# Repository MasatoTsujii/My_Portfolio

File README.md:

# My Portfolio

## はじめに
本リポジトリは、「アイデア対決・全国高等専門学校ロボットコンテスト（高専ロボコン）」における個人の活動や技術をまとめたポートフォリオ。

主に**回路設計** と **組込みソフトウェア** を担当した。

## 技術要素

| Category | Technology / Tools |
| :--- | :--- |
| **Languages** | C++, C |
| **Firmware** | mbed, PlatformIO, Arduino |
| **Hardware CAD** | KiCad, EAGLE |
| **MCU / Modules** | STM32 (Nucleo), PIC, IM920sL (920MHz), Bluetooth |
| **Others** | Git, VSCode, CAN通信 |

## プロジェクト一覧 (Projects)

各プロジェクトの詳細（ソースコード、回路図、開発背景）は、リンク先のディレクトリに格納。

| Year | Project / Role | Key Technologies |
| :--- | :--- | :--- |
| **2022** | **[Season2022: 自作コントローラー](./Season2022)**<br>操作性向上のための専用ハードウェア開発 | 無線通信, **自作コントローラー**, KiCad |
| **2020** | **[Season2020: ちゃぶ台返しロボット](./Season2020)**<br>ダイレクトティーチングの実装とアーム制御 | **ダイレクトティーチング**, **アーム制御**, mbed, PlatformIO, Eagle |
| **2019** | **[OffSeason2019: オフシーズンプロジェクト](./OffSeason2019)**<br>次期シーズンに向けた要素技術の開発と検証 | モータドライバ設計, 回路設計, EAGLE |
| **2019** | **[Season2019: 洗濯物干しロボット](./Season2019)**<br>初の手動ロボット製作 | 機構理解, チーム開発 |
| **2019-2022** | **[MotorDriver_Projects: モータドライバ開発の軌跡](./MotorDriver_Projects)**<br>自作モータドライバの設計と改良 | **CAN通信**, モータドライバ設計, KiCad, EAGLE, STM32 |

## ハイライト

### 1. 通信環境と操作性の課題解決 (Season2022)
**課題:** 10基の砲塔を個別制御するためのボタン不足と、現地会場での電波干渉（2.4GHz帯）のリスク。

**解決策:**
* **専用コントローラーの自作:** 市販品では不可能なボタン配置と機能を実装。
* **920MHz帯の採用:** 混信に強いIM920sLモジュールを採用し、通信プロトコルを独自に実装・改良。大会での通信エラーはなかった。
* [詳細はこちら](./Season2022)

### 2. ダイレクトティーチングの実装 (Season2020)
**課題:** コロナ禍による活動制限で、複雑なモーションプログラムを組む時間が不足。

**解決策:**
* **直感的な教示システム:** ロボットのアームを手で動かして軌道を記録・再生する機能を実装。
* **成果:** プログラムが書けないメンバーでも演出作成が可能になり、開発効率を向上。「本田技研工業特別賞」を受賞した。
* [詳細はこちら](./Season2020)

### 3. モータドライバの設計と最適化 (MotorDriver_Projects)
**課題:** チーム内での回路のメンテナンス性向上と、通信ノイズによる誤動作の防止。

**解決策:**
* **制御方式:** マイコン1基につき1つのドライバを制御する方式でドライバ内のスイッチを使用し、動作確認を行えるように改良。
* **通信方式とツールの移行:** 通信方式をSPIからノイズに強いCAN通信へ変更し、設計ツールもEAGLEからKiCadへと移行して最適化を図った。
* [詳細はこちら](./MotorDriver_Projects)

---
*Author: [Your Name]*

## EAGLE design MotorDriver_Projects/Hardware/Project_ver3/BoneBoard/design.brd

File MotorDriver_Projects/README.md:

# MotorDriver_Projects

## 概要
これまで作成した表面実装基板の設計データ、およびテスト用ファームウェアをまとめたディレクトリである。
モータドライバの開発コードネームが「Mars（火星）」であったことを発端に、以降製作された電磁弁駆動基板など周辺回路にも惑星の名前が付けられている。
各基板プロジェクトには、CADの元データのほか、閲覧用の回路図（PDF等）および基板レイアウト図が同梱されている。

## ディレクトリ構成とプロジェクトの変遷

### 1. Project_ver1
* **開発ツール:** EAGLE
* **`MD_Mars_ver1`**
    先輩が設計した初期型モータドライバ。メインマイコンに表面実装タイプのPICを採用しており、通信方式はSPIである。

### 2. Project_ver2
* **開発ツール:** EAGLE
* **`MD_Mars_ver2`**
    先輩の`ver1`をベースに、自身で再設計を行ったモデル。製作のしやすさや大会現場でのメンテナンス性を考慮し、マイコンを表面実装からDIP（ピン）タイプのPICへと変更した。通信方式はSPIを継承している。
* **`MD_Mars_study`**
    モータドライバの回路構成や仕組みを深く理解するために自作した学習用基板。部内のCNCルーターで切削加工して製作したが、設計したランド（銅箔部）が細すぎたため、大電流を流した際に焼損した。失敗からプリント基板におけるパターン幅の重要性を学んだ基板である。

### 3. Project_ver3
* **開発ツール:** EAGLE
* **アーキテクチャの刷新**
    「各モータドライバに1つずつマイコンを載せる」方式を廃止し、「1つのメインマイコンで複数のモータドライバを集中制御する」方式へと仕様を大きく変更した。PCのメモリのように、拡張基板に対してドライバを垂直に突き刺して使用する設計を採用している。以下の3つの基板から構成される。
    * **`MD_Mars_ver3`:** モータ駆動回路のみを切り出し、小型化を図ったドライバモジュール。
    * **`MarsBrain`:** メインマイコンからの制御信号を各モータドライバへ分配するための拡張基板。
    * **`BoneBoard`:** メインマイコンとモータドライバ群を相互に接続するためのバックプレーン（骨格）基板。

### 4. Project_ver4
* **開発ツール:** KiCad
* **アーキテクチャの再構築と最適化**
    設計ツールをKiCadへ移行。通信方式をノイズに強いCAN通信へと変更し、新たにゲートドライバICを採用したアップデート版である。
    * **`MD_Mars_ver4_prototype`**
        新規採用したゲートドライバの動作を検証するために、部内CNCで切削加工したテスト基板。この基板で確実な動作確認を行った後、本番機の実装へ進んだ。
    * **`MD_Mars_ver4.0.0`**
        メインマイコンにSTM32F303K8を採用した新基板。タクトスイッチやトグルスイッチを実装し、PCに繋がなくてもCANのID設定やモータの単体動作確認をハードウェア上で行えるよう設計した。
    * **`MD_Mars_ver4.1.0`**
        `ver4.0.0`の基板発注前にチーム内で協議し、回路配置や配線をさらに最適化した最終バージョン。実際の大会ロボットにはこの基板が搭載され、運用された。

### 5. Other (周辺回路基板)
モータドライバ以外の機能を持つ表面実装基板群である。
* **`Jupiter_12V`:** 12V駆動の電磁弁制御用基板。
* **`Jupiter_24V`:** 24V駆動の電磁弁制御用基板。
* **`PowerPlatform_24Vto5V`:** 24VのLiPoバッテリー電源から5Vへ降圧するための電源変換基板（実戦での使用実績はなし）。

---

## Firmware (テスト用プログラム)

当時のモータドライバ開発は複数人での分業プロジェクトであったため、本ディレクトリに含まれるファームウェアは自身が検証用に担当した部分のみとなっている。

* **`Mars_ver4.00_Test`**
    `MD_Mars_ver4_prototype`基板を用いて、新たに導入したゲートドライバおよびモータ駆動のハードウェア動作確認を行うために作成したテスト用プログラムである。platformioを使用。

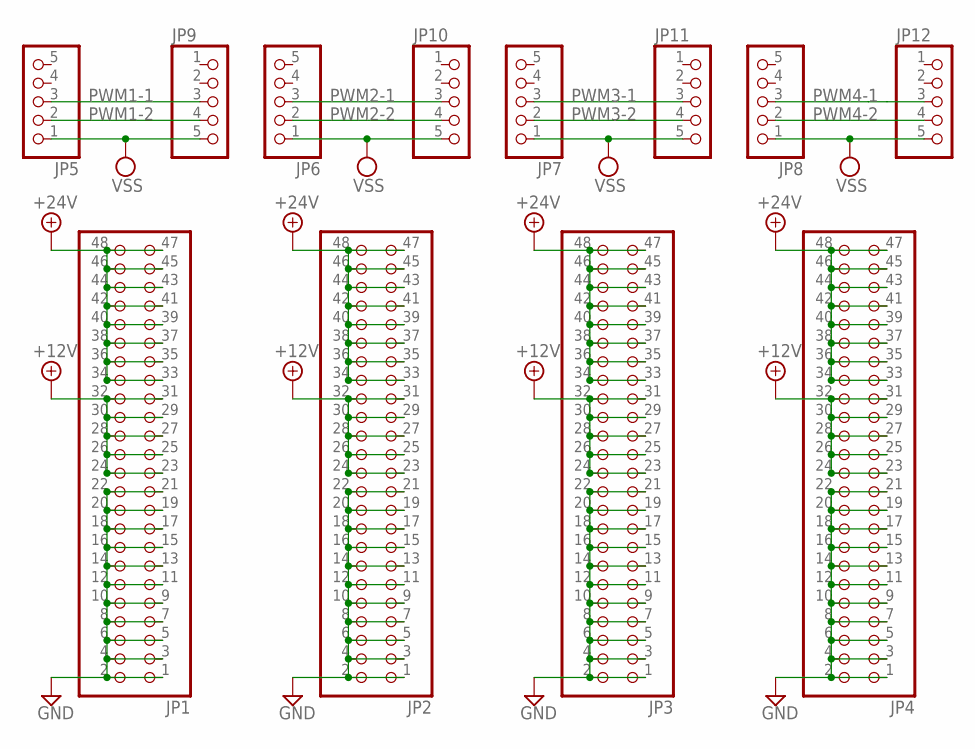
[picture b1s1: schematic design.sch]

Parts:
JP1, JP2, JP3, JP4: PINHD-2X24; 2X24
JP5, JP6, JP7, JP8: PINHD-1X5; 1X05
JP9, JP10, JP11, JP12: PINHD-1X5/90; 1X05/90

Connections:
+12V: JP1.23, JP1.24, JP1.25, JP1.26, JP1.27, JP1.28, JP1.29, JP1.30, JP1.31, JP1.32, JP2.23, JP2.24, JP2.25, JP2.26, JP2.27, JP2.28, JP2.29, JP2.30, JP2.31, JP2.32, JP3.23, JP3.24, JP3.25, JP3.26, JP3.27, JP3.28, JP3.29, JP3.30, JP3.31, JP3.32, JP4.23, JP4.24, JP4.25, JP4.26, JP4.27, JP4.28, JP4.29, JP4.30, JP4.31, JP4.32
+24V: JP1.33, JP1.34, JP1.35, JP1.36, JP1.37, JP1.38, JP1.39, JP1.40, JP1.41, JP1.42, JP1.43, JP1.44, JP1.45, JP1.46, JP1.47, JP1.48, JP2.33, JP2.34, JP2.35, JP2.36, JP2.37, JP2.38, JP2.39, JP2.40, JP2.41, JP2.42, JP2.43, JP2.44, JP2.45, JP2.46, JP2.47, JP2.48, JP3.33, JP3.34, JP3.35, JP3.36, JP3.37, JP3.38, JP3.39, JP3.40, JP3.41, JP3.42, JP3.43, JP3.44, JP3.45, JP3.46, JP3.47, JP3.48, JP4.33, JP4.34, JP4.35, JP4.36, JP4.37, JP4.38, JP4.39, JP4.40, JP4.41, JP4.42, JP4.43, JP4.44, JP4.45, JP4.46, JP4.47, JP4.48
GND: JP1.1, JP1.2, JP1.3, JP1.4, JP1.5, JP1.6, JP1.7, JP1.8, JP1.9, JP1.10, JP1.11, JP1.12, JP1.13, JP1.14, JP1.15, JP1.16, JP1.17, JP1.18, JP1.19, JP1.20, JP1.21, JP1.22, JP2.1, JP2.2, JP2.3, JP2.4, JP2.5, JP2.6, JP2.7, JP2.8, JP2.9, JP2.10, JP2.11, JP2.12, JP2.13, JP2.14, JP2.15, JP2.16, JP2.17, JP2.18, JP2.19, JP2.20, JP2.21, JP2.22, JP3.1, JP3.2, JP3.3, JP3.4, JP3.5, JP3.6, JP3.7, JP3.8, JP3.9, JP3.10, JP3.11, JP3.12, JP3.13, JP3.14, JP3.15, JP3.16, JP3.17, JP3.18, JP3.19, JP3.20, JP3.21, JP3.22, JP4.1, JP4.2, JP4.3, JP4.4, JP4.5, JP4.6, JP4.7, JP4.8, JP4.9, JP4.10, JP4.11, JP4.12, JP4.13, JP4.14, JP4.15, JP4.16, JP4.17, JP4.18, JP4.19, JP4.20, JP4.21, JP4.22
PWM1-1: JP5.3, JP9.3
PWM1-2: JP5.2, JP9.4
PWM2-1: JP6.3, JP10.3
PWM2-2: JP6.2, JP10.4
PWM3-1: JP7.3, JP11.3
PWM3-2: JP7.2, JP11.4
PWM4-1: JP8.3, JP12.3
PWM4-2: JP8.2, JP12.4
VSS: JP5.1, JP6.1, JP7.1, JP8.1, JP9.5, JP10.5, JP11.5, JP12.5

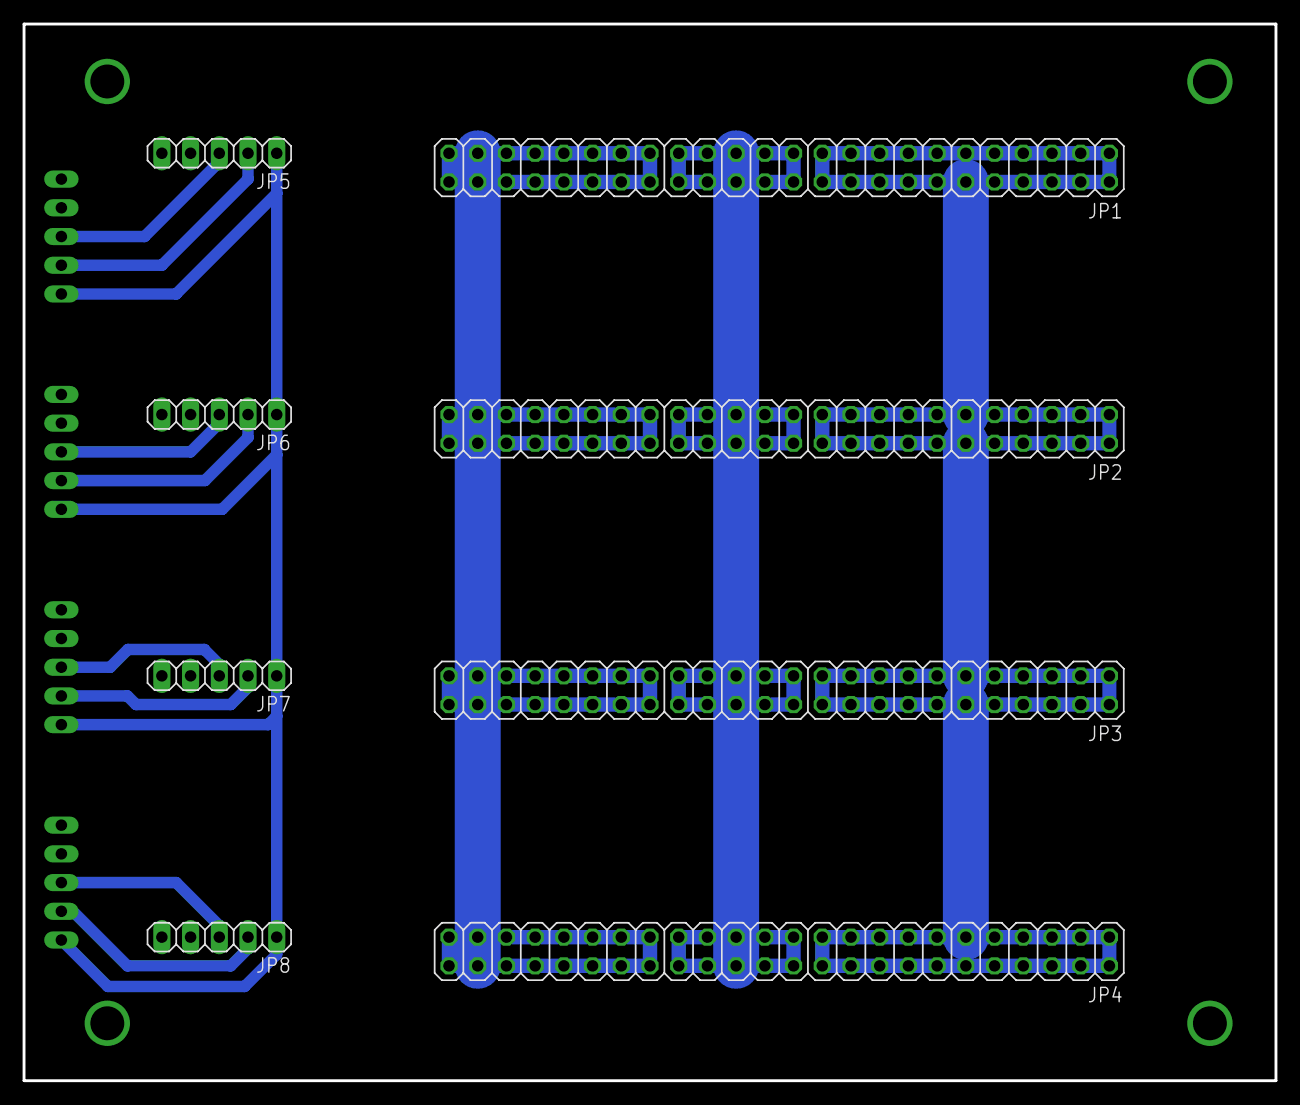
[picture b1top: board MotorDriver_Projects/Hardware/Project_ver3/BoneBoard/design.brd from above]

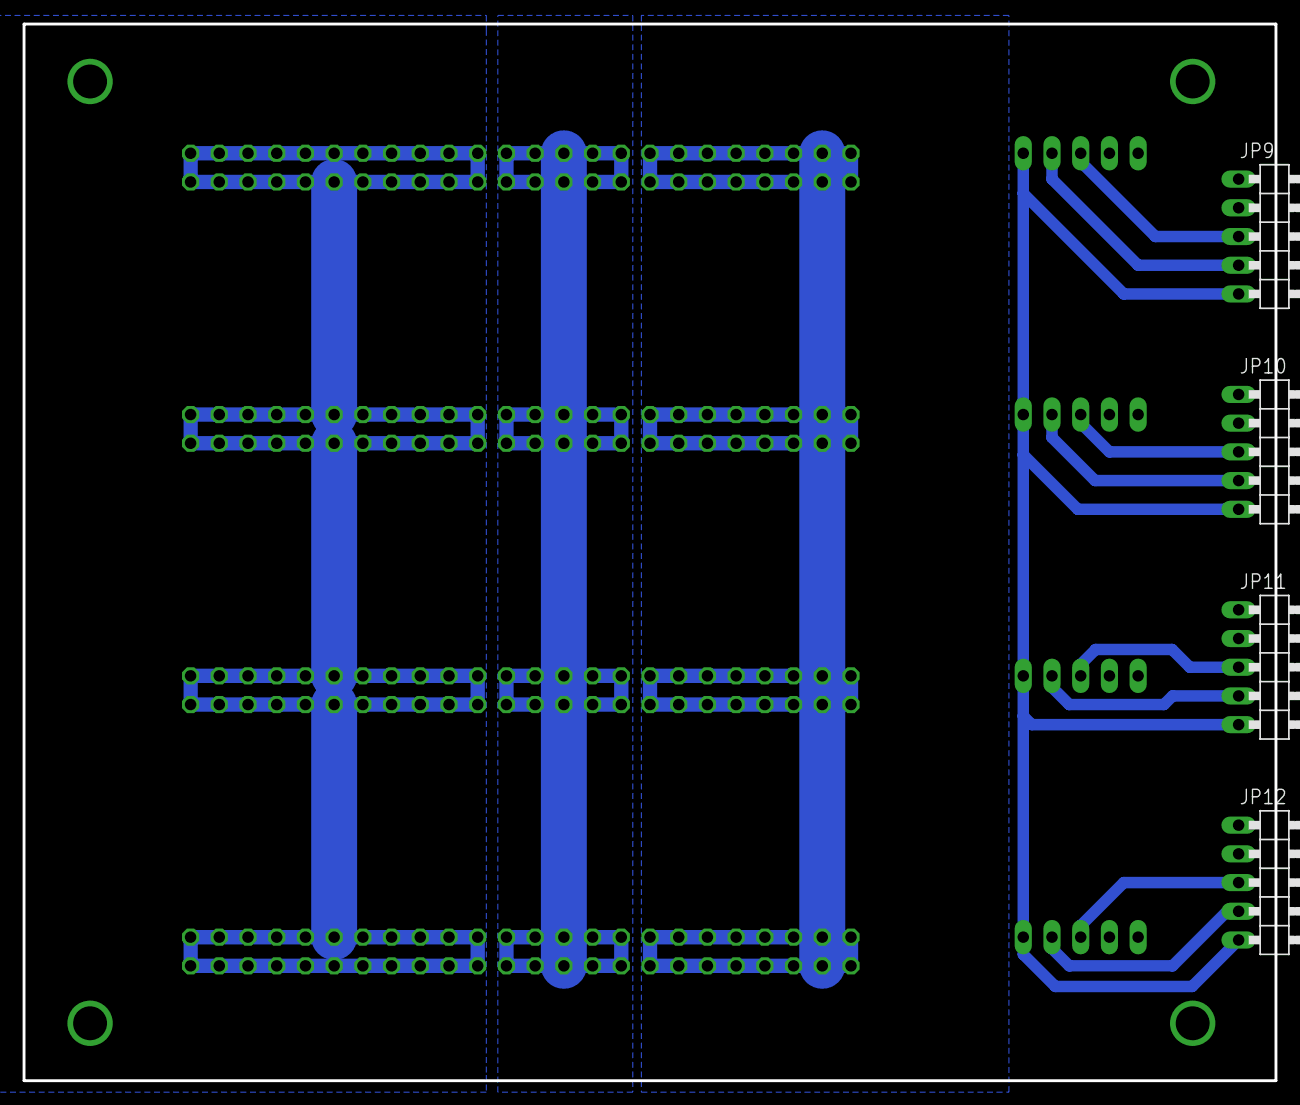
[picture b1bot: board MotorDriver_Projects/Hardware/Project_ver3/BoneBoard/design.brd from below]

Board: 2 copper layers, 110.7 x 93.5 mm, 12 parts (4 on the bottom side), 12 nets.

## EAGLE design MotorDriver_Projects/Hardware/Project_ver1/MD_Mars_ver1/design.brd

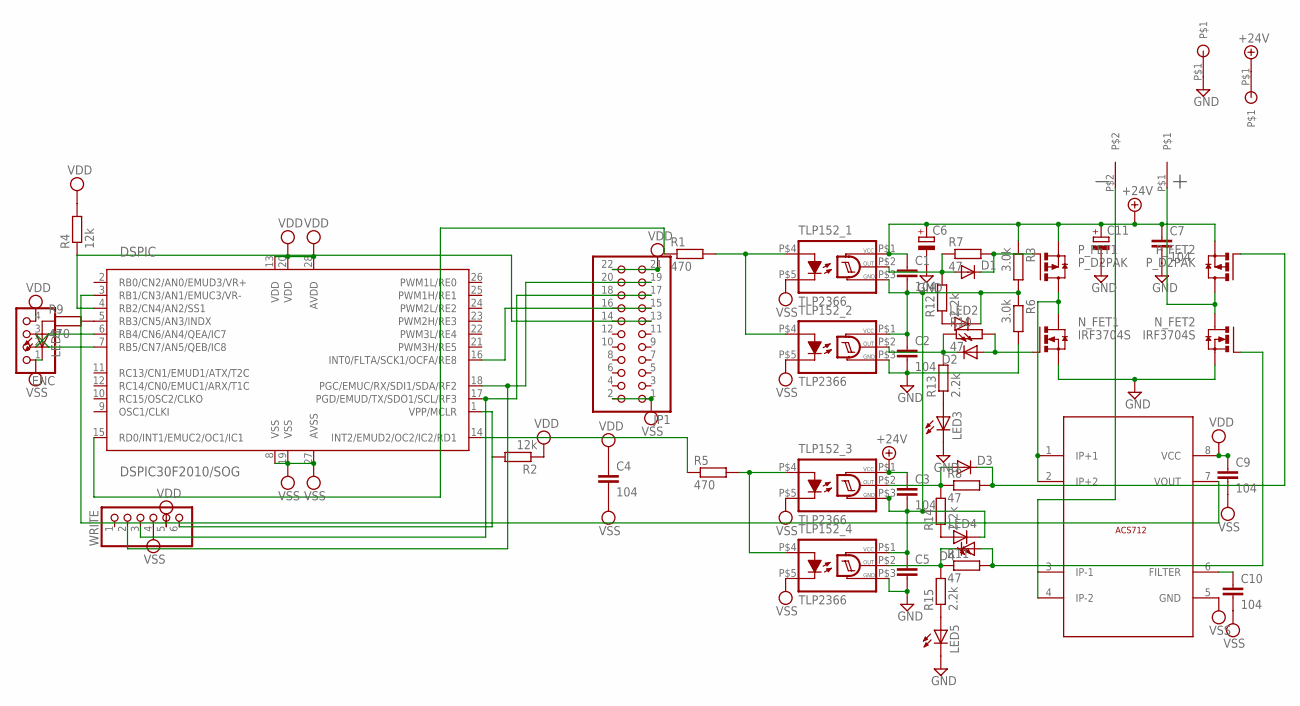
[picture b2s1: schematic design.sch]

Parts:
ACS712: ACS712ELCTR-30A-T; SO8
C1, C2, C3, C4, C7, C9, C10: 104; C2012
C5: CC2012; C2012
C6: CPOL-EUTAP5-70; TAP5-70
C11: CPOL-EUE5-13; E5-13
D1, D2, D3, D4: DIODE-SOD123; SOD123
DSPIC: DSPIC30F2010/SOG; SO-28W
ENC: PINHD-1X4/90; 1X04/90
JP1: PINHD-2X11/90; 2X11/90
LED1, LED2, LED3, LED4, LED5: LEDCHIP-LED0603; CHIP-LED0603
N_FET1, N_FET2: IRF3704S; D2PACK
P_FET1, P_FET2: P_D2PAK; D2PACK
R1, R5, R9: 470; M0805
R2, R4: 12k; M0805
R3, R6: 3.0k; M0805
R7, R8, R10, R11: 47; M0805
R12, R13, R14, R15: 2.2k; M0805
TLP152_1, TLP152_2, TLP152_3, TLP152_4: TLP2366; SO6
U$1: XT60PW
U$8, U$9: MARU
WRITE: PINHD-1X6/90; 1X06/90

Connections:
+24V: C1.1, C3.1, C6.+, C7.1, C11.+, P_FET1.3 (S), P_FET2.3 (S), R3.1, TLP152_1.P$1 (VCC), TLP152_3.P$1 (VCC), U$8.P$1
GND: C2.2, C5.2, C6.-, C7.2, C11.-, LED3.C, LED5.C, N_FET1.3 (S), N_FET2.3 (S), R6.2, TLP152_2.P$3 (GND), TLP152_4.P$3 (GND), U$9.P$1
unnamed: R1.2, TLP152_1.P$4 (A), TLP152_2.P$4 (A)
unnamed: R5.2, TLP152_3.P$4 (A), TLP152_4.P$4 (A)
unnamed: DSPIC.15 (RD0/INT1/EMUC2/OC1/IC1), R1.1
unnamed: LED1.A, R9.1
unnamed: D1.A, R7.1, R12.2, TLP152_1.P$2 (OUT)
unnamed: DSPIC.1 (VPP/MCLR), R2.2, WRITE.6
unnamed: D2.C, R10.1, R13.2, TLP152_2.P$2 (OUT)
unnamed: D2.A, N_FET1.1 (G), R10.2
unnamed: ACS712.1 (IP+1), ACS712.2 (IP+2), N_FET1.2 (D), P_FET1.2 (D)
unnamed: C1.2, C2.1, C3.2, C5.1, LED2.C, LED4.C, R3.2, R6.1, TLP152_1.P$3 (GND), TLP152_2.P$1 (VCC), TLP152_3.P$3 (GND), TLP152_4.P$1 (VCC)
unnamed: DSPIC.6 (RB4/CN6/AN4/QEA/IC7), ENC.2
unnamed: DSPIC.14 (INT2/EMUD2/OC2/IC2/RD1), R5.1
unnamed: D1.C, P_FET1.1 (G), R7.2
unnamed: DSPIC.7 (RB5/CN7/AN5/QEB/IC8), ENC.3
unnamed: DSPIC.4 (RB2/CN4/AN2/SS1), JP1.13, JP1.14, R4.1
unnamed: LED2.A, R12.1
unnamed: ACS712.6 (FILTER), C10.1
unnamed: DSPIC.5 (RB3/CN5/AN3/INDX), R9.2
unnamed: LED3.A, R13.1
unnamed: D3.A, R8.1, R14.2, TLP152_3.P$2 (OUT)
unnamed: D4.C, R11.1, R15.2, TLP152_4.P$2 (OUT)
unnamed: DSPIC.16 (INT0/FLTA/SCK1/OCFA/RE8), JP1.15, JP1.16
unnamed: D4.A, N_FET2.1 (G), R11.2
unnamed: D3.C, P_FET2.1 (G), R8.2
unnamed: ACS712.7 (VOUT), DSPIC.3 (RB1/CN3/AN1/EMUC3/VR-)
unnamed: LED4.A, R14.1
unnamed: ACS712.3 (IP-1), ACS712.4 (IP-2), U$1.P$2
unnamed: DSPIC.17 (PGD/EMUD/TX/SDO1/SCL/RF3), JP1.17, JP1.18, WRITE.3
unnamed: LED5.A, R15.1
unnamed: N_FET2.2 (D), P_FET2.2 (D), U$1.P$1
unnamed: DSPIC.18 (PGC/EMUC/RX/SDI1/SDA/RF2), JP1.19, JP1.20, WRITE.2
VDD: ACS712.8 (VCC), C4.1, C9.1, DSPIC.13 (VDD), DSPIC.20 (VDD), DSPIC.28 (AVDD), ENC.4, JP1.21, JP1.22, R2.1, R4.2, WRITE.5
VSS: ACS712.5 (GND), C4.2, C9.2, C10.2, DSPIC.8 (VSS), DSPIC.19 (VSS), DSPIC.27 (AVSS), ENC.1, JP1.1, JP1.2, LED1.C, TLP152_1.P$5 (C), TLP152_2.P$5 (C), TLP152_3.P$5 (C), TLP152_4.P$5 (C), WRITE.4

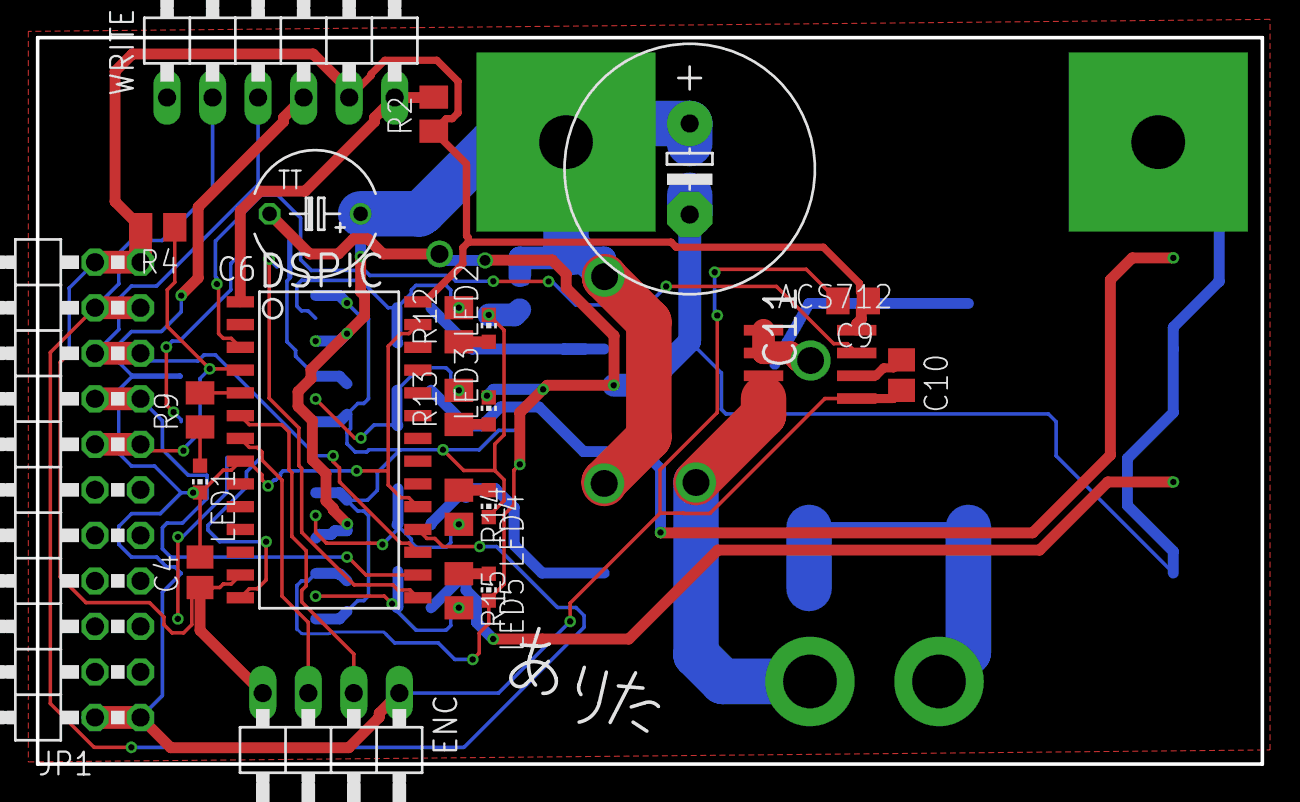
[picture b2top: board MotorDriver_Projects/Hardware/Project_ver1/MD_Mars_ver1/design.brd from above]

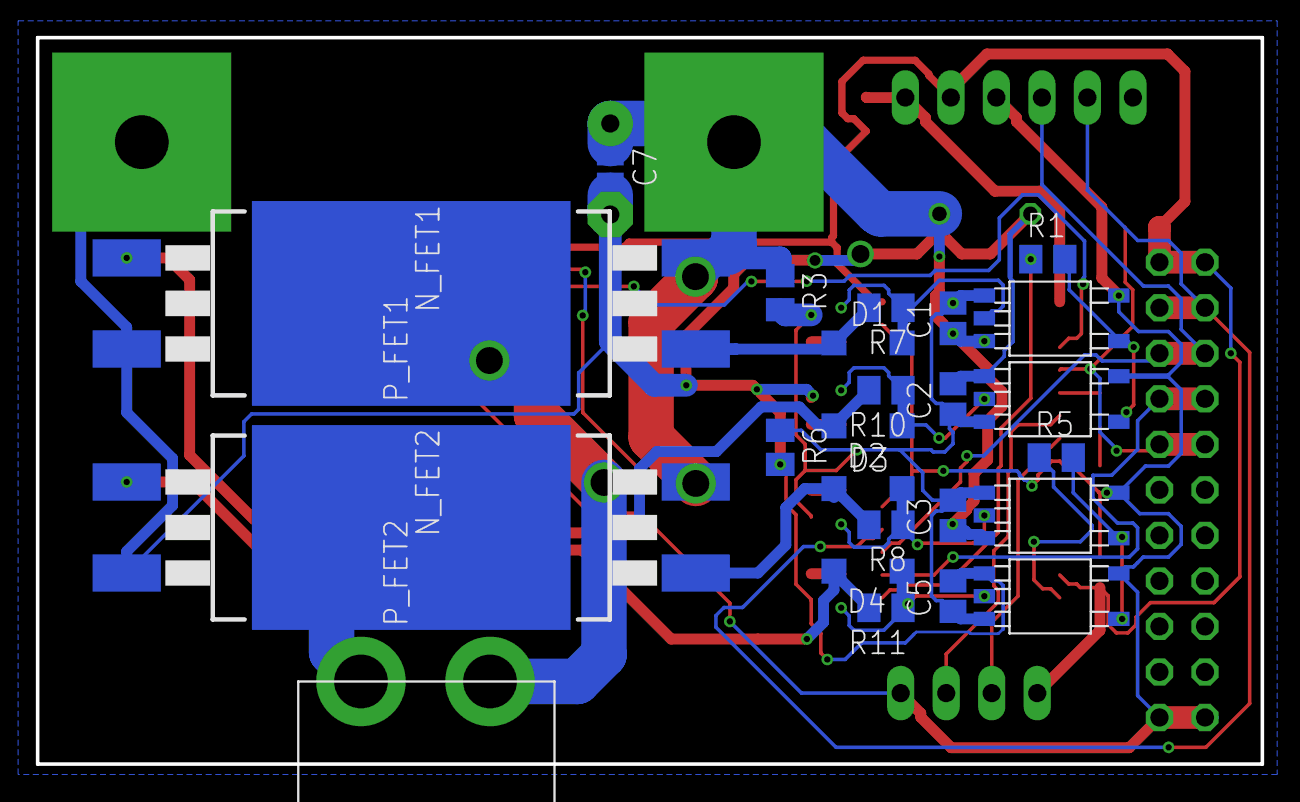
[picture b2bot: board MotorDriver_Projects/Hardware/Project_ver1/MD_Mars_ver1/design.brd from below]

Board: 2 copper layers, 68.3 x 40.5 mm, 50 parts (25 on the bottom side), 35 nets.

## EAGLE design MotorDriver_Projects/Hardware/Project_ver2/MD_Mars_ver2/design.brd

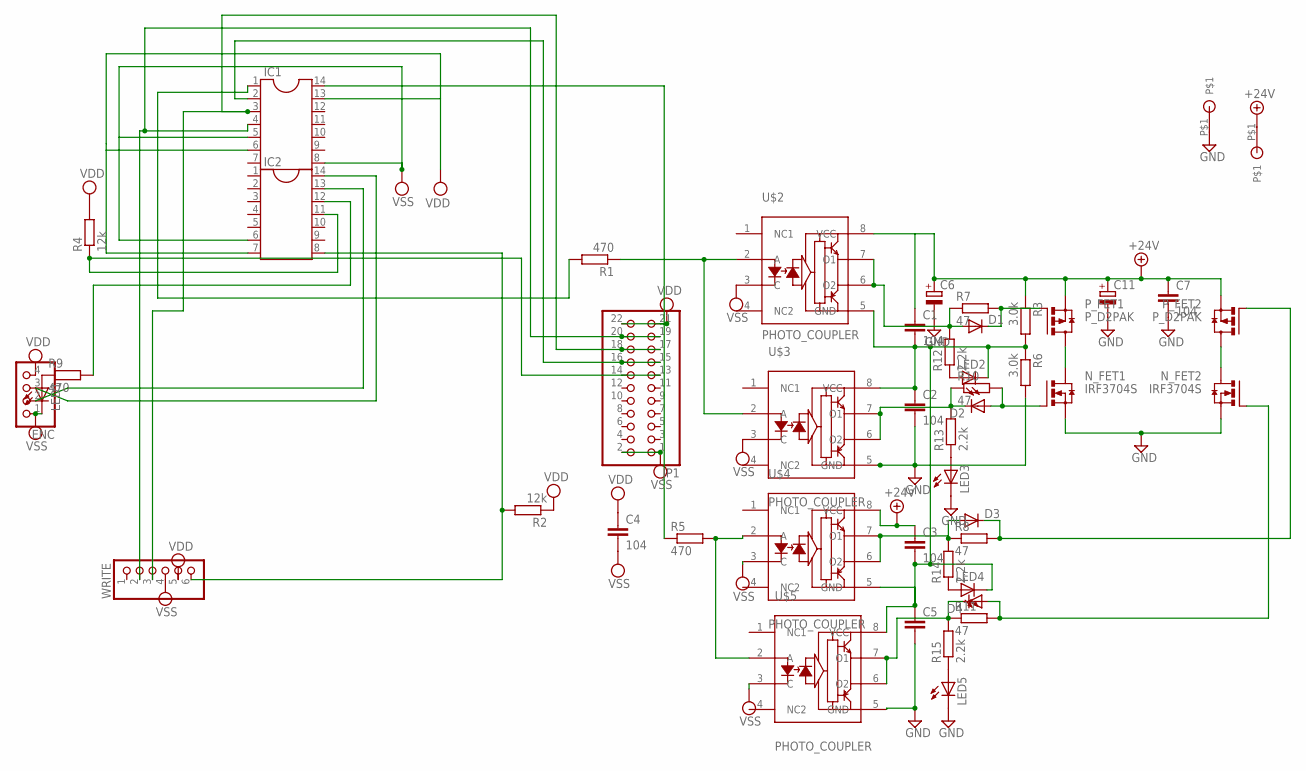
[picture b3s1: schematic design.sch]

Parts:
C1, C2, C3, C4, C7: 104; C2012
C5: CC2012; C2012
C6: CPOL-EUTAP5-70; TAP5-70
C11: CPOL-EUE5-13; E5-13
D1, D2, D3, D4: DIODE-SOD123; SOD123
ENC: PINHD-1X4/90; 1X04/90
IC1, IC2: DIL14S; SOCKET-14
JP1: PINHD-2X11/90; 2X11/90
LED1, LED2, LED3, LED4, LED5: LEDCHIP-LED0603; CHIP-LED0603
N_FET1, N_FET2: IRF3704S; D2PACK
P_FET1, P_FET2: P_D2PAK; D2PACK
R1, R5, R9: 470; M0805
R2, R4: 12k; M0805
R3, R6: 3.0k; M0805
R7, R8, R10, R11: 47; M0805
R12, R13, R14, R15: 2.2k; M0805
U$2, U$3, U$4, U$5: PHOTO_COUPLER; DIL08
U$8, U$9: MARU
WRITE: PINHD-1X6/90; 1X06/90

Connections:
+24V: C1.1, C3.1, C6.+, C7.1, C11.+, P_FET1.3 (S), P_FET2.3 (S), R3.1, U$2.8 (VCC), U$4.8 (VCC), U$8.P$1
GND: C2.2, C5.2, C6.-, C7.2, C11.-, LED3.C, LED5.C, N_FET1.3 (S), N_FET2.3 (S), R6.2, U$3.5 (GND), U$5.5 (GND), U$9.P$1
unnamed: IC1.1, R1.2
unnamed: R5.2, U$4.2 (A), U$5.2 (A)
unnamed: R1.1, U$2.2 (A), U$3.2 (A)
unnamed: LED1.A, R9.1
unnamed: IC1.14, R5.1
unnamed: IC2.8, R2.2, WRITE.6
unnamed: D2.C, R10.1, R13.2, U$3.6 (O2), U$3.7 (O1)
unnamed: D2.A, N_FET1.1 (G), R10.2
unnamed: N_FET1.2 (D), P_FET1.2 (D)
unnamed: C1.2, C2.1, C3.2, C5.1, LED2.C, LED4.C, R3.2, R6.1, U$2.5 (GND), U$3.8 (VCC), U$4.5 (GND), U$5.8 (VCC)
unnamed: ENC.3, IC2.14
unnamed: D4.C, R11.1, R15.2, U$5.6 (O2), U$5.7 (O1)
unnamed: D1.A, R7.1, R12.2, U$2.6 (O2), U$2.7 (O1)
unnamed: D3.A, R8.1, R14.2, U$4.6 (O2), U$4.7 (O1)
unnamed: IC2.12, R9.2
unnamed: D1.C, P_FET1.1 (G), R7.2
unnamed: ENC.2, IC2.13
unnamed: IC1.2, JP1.15, JP1.16
unnamed: IC2.11, JP1.13, JP1.14, R4.1
unnamed: LED2.A, R12.1
unnamed: IC1.3, JP1.17, JP1.18, WRITE.3
unnamed: IC1.4, JP1.19, JP1.20, WRITE.2
unnamed: LED3.A, R13.1
unnamed: D4.A, N_FET2.1 (G), R11.2
unnamed: D3.C, P_FET2.1 (G), R8.2
unnamed: LED4.A, R14.1
unnamed: LED5.A, R15.1
unnamed: N_FET2.2 (D), P_FET2.2 (D)
VDD: C4.1, ENC.4, IC1.6, IC1.13, IC2.7, JP1.21, JP1.22, R2.1, R4.2, WRITE.5
VSS: C4.2, ENC.1, IC1.5, IC1.8, IC2.6, JP1.1, JP1.2, LED1.C, U$2.3 (C), U$3.3 (C), U$4.3 (C), U$5.3 (C), WRITE.4

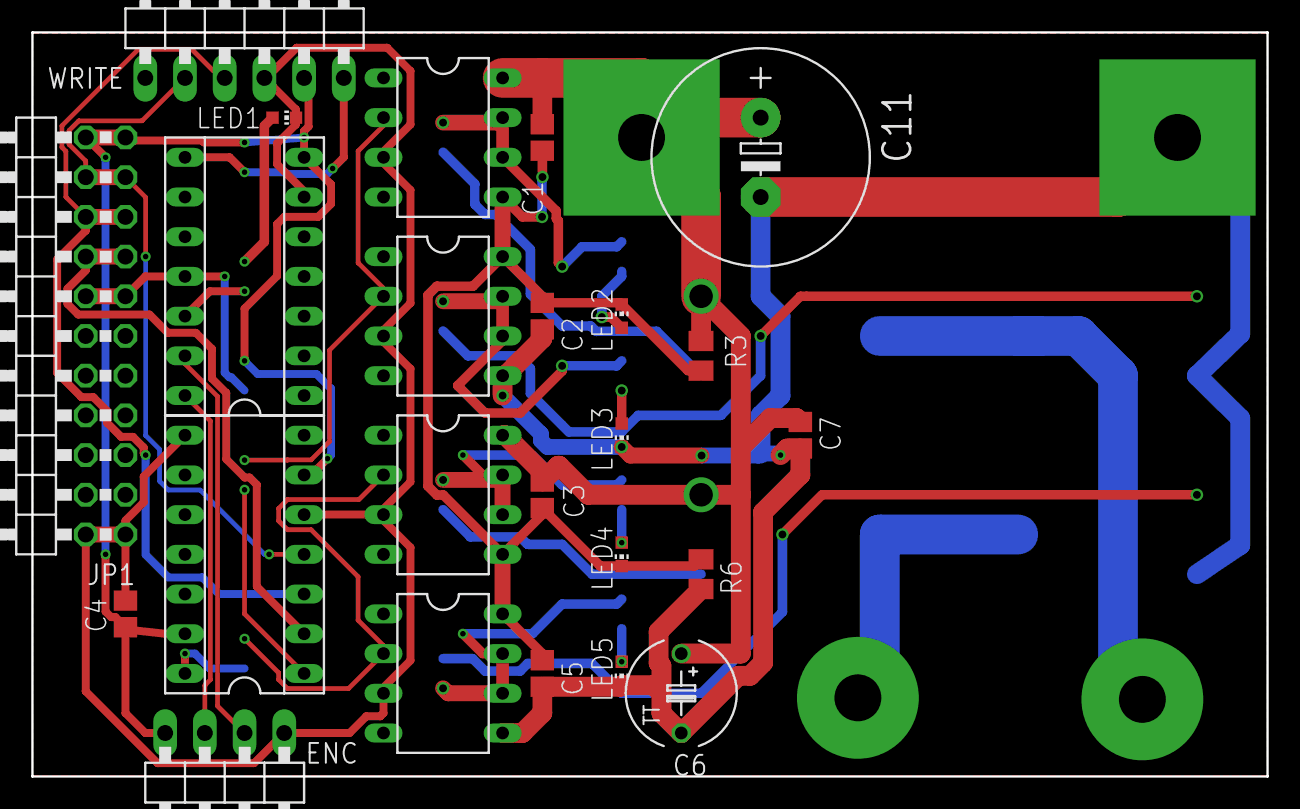
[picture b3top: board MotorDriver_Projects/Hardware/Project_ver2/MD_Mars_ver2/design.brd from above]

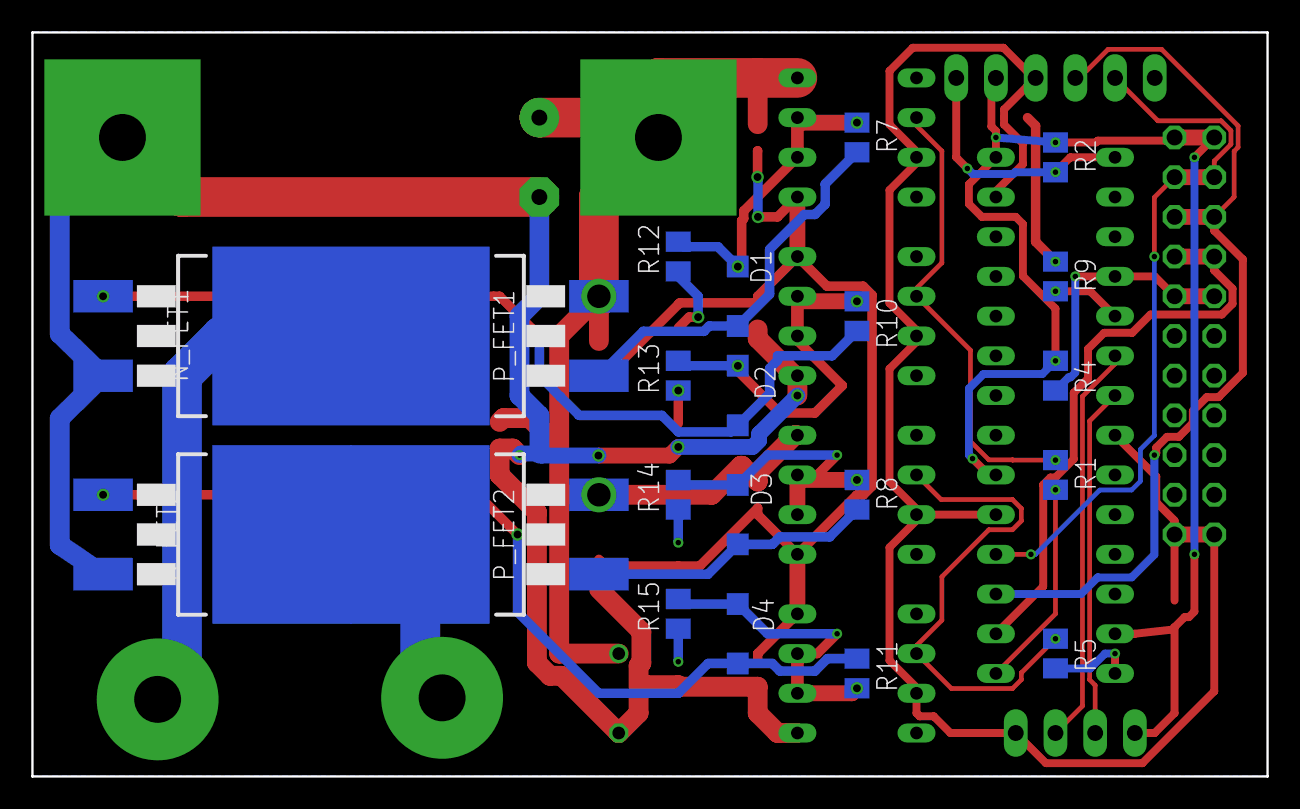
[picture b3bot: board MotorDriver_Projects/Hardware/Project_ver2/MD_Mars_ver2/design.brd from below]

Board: 2 copper layers, 79.0 x 47.6 mm, 47 parts (21 on the bottom side), 32 nets.

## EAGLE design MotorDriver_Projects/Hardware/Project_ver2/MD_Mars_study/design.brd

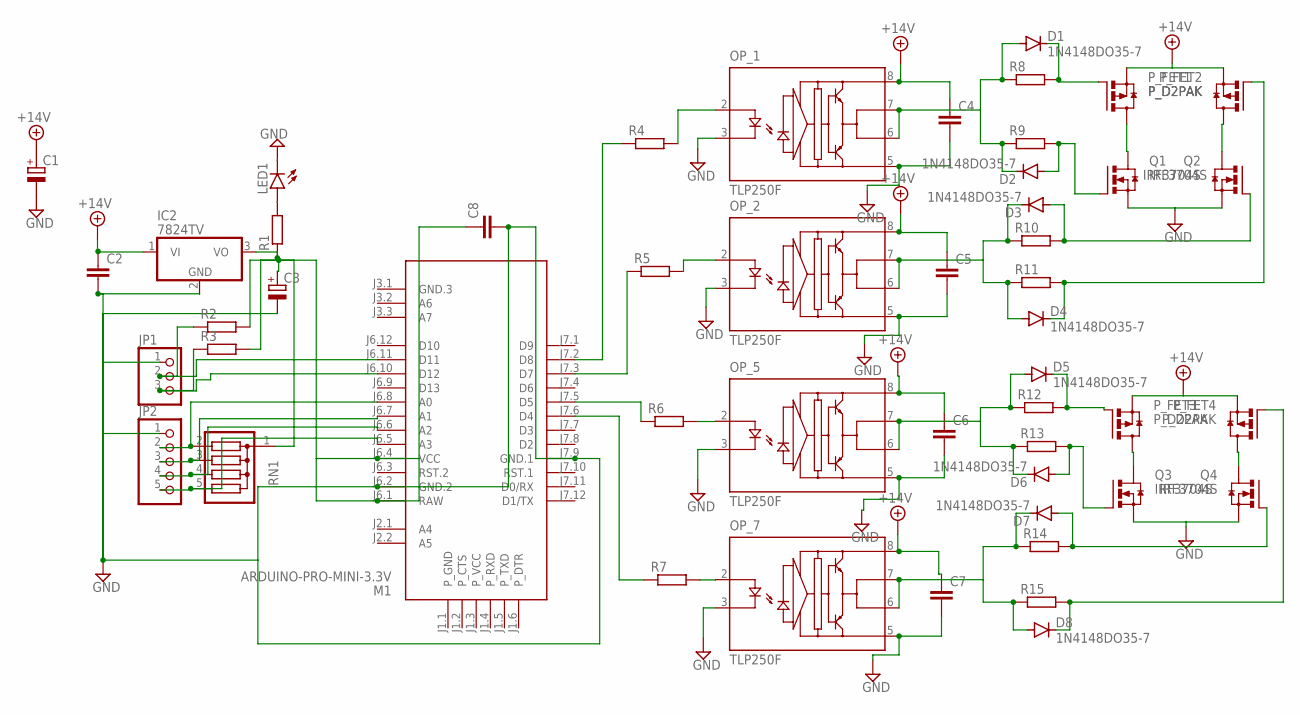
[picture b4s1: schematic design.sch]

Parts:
C1: CPOL-EUE5-13; E5-13
C2, C4, C5, C6, C7, C8: C-EU050-024X044; C050-024X044
C3: CPOL-EUE2.5-5; E2,5-5
D1, D2, D3, D4, D5, D6, D7, D8: 1N4148DO35-7; DO35-7
IC2: 7824TV; TO220V
JP1: PINHD-1X3; 1X03
JP2: PINHD-1X5; 1X05
LED1: LED5MM
M1: ARDUINO-PRO-MINI-3.3V; ARDUINO-PRO-MINI
OP_1, OP_2, OP_5, OP_7: TLP250F; DIL08
P_FET1, P_FET2, P_FET3, P_FET4: P_D2PAK; D2PACK
Q1, Q2, Q3, Q4: IRF3704S; D2PACK
R1, R2, R3, R4, R5, R6, R7, R8, R9, R10, R11, R12, R13, R14, R15: R-EU_0207/7; 0207/7
RN1: G04R; SIL5

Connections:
+14V: C1.+, C2.1, C4.1, C5.1, C6.1, C7.1, IC2.1 (VI), OP_1.8 (VCC), OP_2.8 (VCC), OP_5.8 (VCC), OP_7.8 (VCC), P_FET1.3 (S), P_FET2.3 (S), P_FET3.3 (S), P_FET4.3 (S)
GND: C1.-, C2.2, C3.-, C4.2, C5.2, C6.2, C7.2, C8.2, IC2.2 (GND), JP1.1, JP2.1, LED1.K (C), M1.J6.2 (GND.2), M1.J7.9 (GND.1), OP_1.3 (K), OP_1.5 (GND), OP_2.3 (K), OP_2.5 (GND), OP_5.3 (K), OP_5.5 (GND), OP_7.3 (K), OP_7.5 (GND), Q1.3 (S), Q2.3 (S), Q3.3 (S), Q4.3 (S)
unnamed: C3.+, C8.1, IC2.3 (VO), M1.J6.1 (RAW), M1.J6.4 (VCC), R1.1, R2.2, R3.2, RN1.1
unnamed: JP1.2, M1.J6.11 (D11), R2.1
unnamed: LED1.A, R1.2
unnamed: JP1.3, M1.J6.10 (D12), R3.1
unnamed: JP2.2, M1.J6.8 (A0), RN1.2
unnamed: JP2.3, M1.J6.7 (A1), RN1.3
unnamed: JP2.4, M1.J6.6 (A2), RN1.4
unnamed: M1.J7.2 (D8), R4.1
unnamed: OP_1.2 (A), R4.2
unnamed: M1.J7.3 (D7), R5.1
unnamed: M1.J7.5 (D5), R6.1
unnamed: OP_2.2 (A), R5.2
unnamed: OP_5.2 (A), R6.2
unnamed: OP_7.2 (A), R7.2
unnamed: M1.J7.6 (D4), R7.1
unnamed: D1.A, D2.C, OP_1.6 (VO), OP_1.7 (VO'), R8.1, R9.1
unnamed: D3.C, D4.A, OP_2.6 (VO), OP_2.7 (VO'), R10.1, R11.1
unnamed: D5.A, D6.C, OP_5.6 (VO), OP_5.7 (VO'), R12.1, R13.1
unnamed: D7.C, D8.A, OP_7.6 (VO), OP_7.7 (VO'), R14.1, R15.1
unnamed: P_FET3.2 (D), Q3.2 (D)
unnamed: D3.A, Q2.1 (G), R10.2
unnamed: D2.A, Q1.1 (G), R9.2
unnamed: D4.C, P_FET2.1 (G), R11.2
unnamed: D5.C, P_FET3.1 (G), R12.2
unnamed: P_FET1.2 (D), Q1.2 (D)
unnamed: D6.A, Q3.1 (G), R13.2
unnamed: D7.A, Q4.1 (G), R14.2
unnamed: P_FET2.2 (D), Q2.2 (D)
unnamed: D8.C, P_FET4.1 (G), R15.2
unnamed: P_FET4.2 (D), Q4.2 (D)
unnamed: D1.C, P_FET1.1 (G), R8.2
unnamed: JP2.5, M1.J6.5 (A3), RN1.5

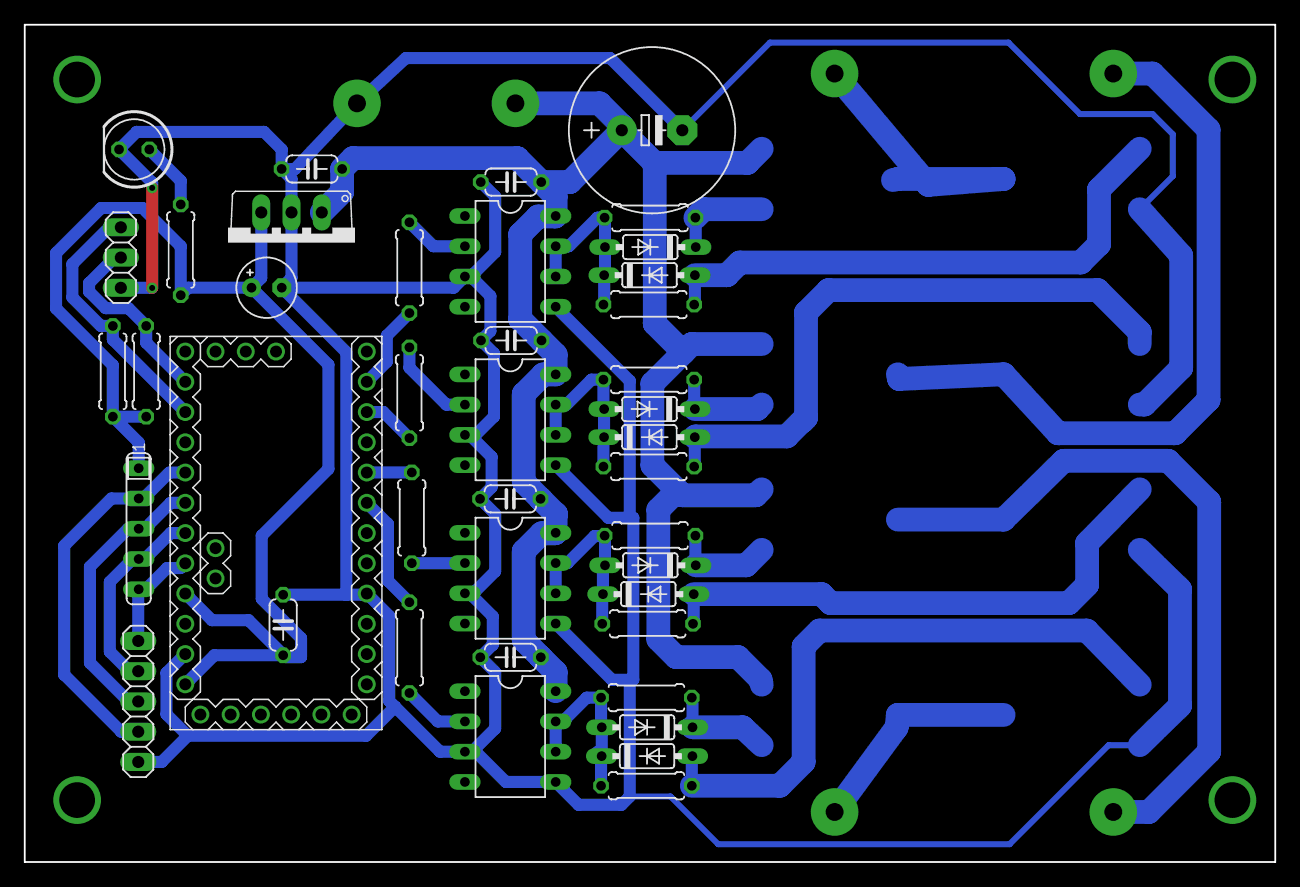
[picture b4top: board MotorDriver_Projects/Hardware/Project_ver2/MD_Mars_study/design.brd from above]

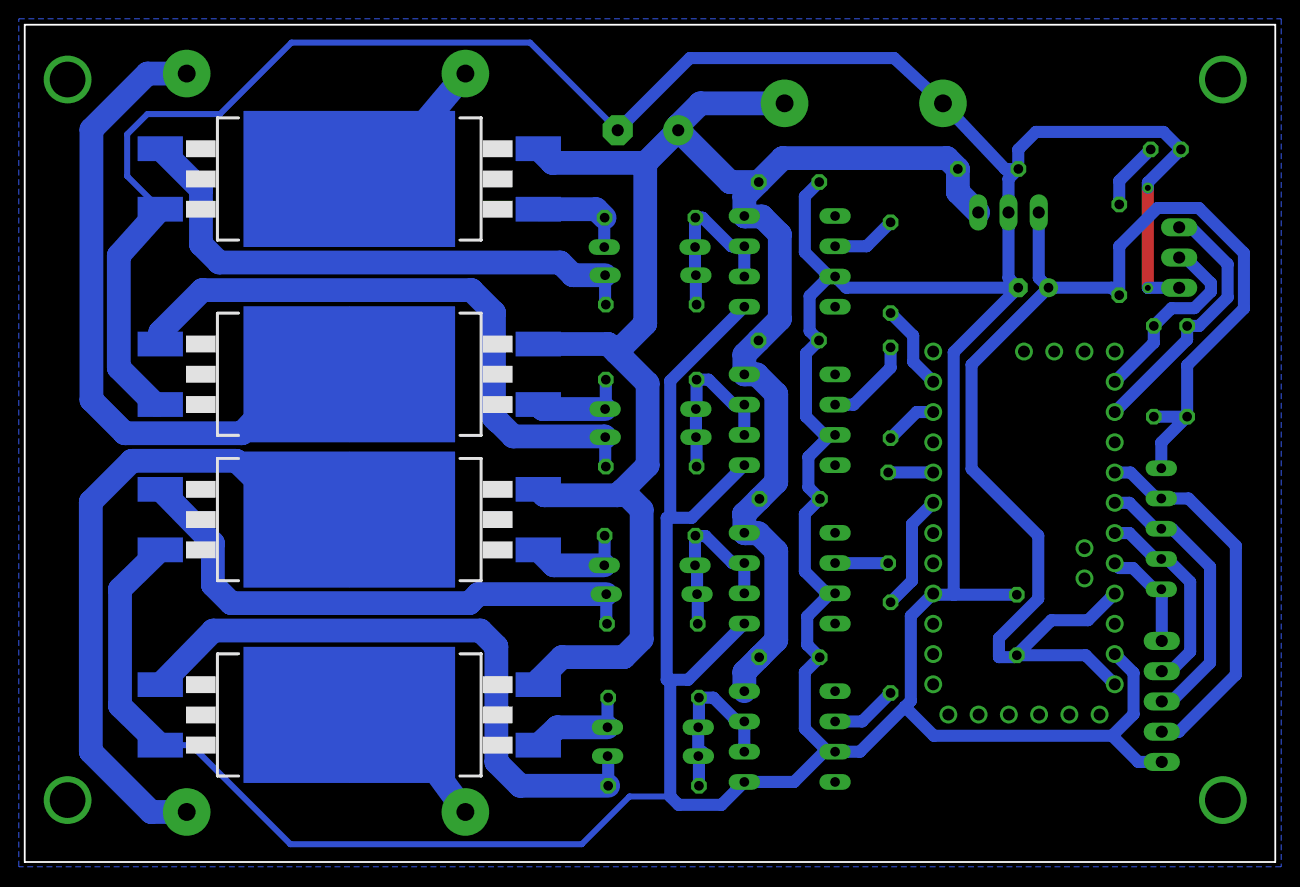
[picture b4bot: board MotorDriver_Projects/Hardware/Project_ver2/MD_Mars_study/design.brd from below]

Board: 2 copper layers, 105.0 x 70.3 mm, 49 parts (8 on the bottom side), 34 nets.

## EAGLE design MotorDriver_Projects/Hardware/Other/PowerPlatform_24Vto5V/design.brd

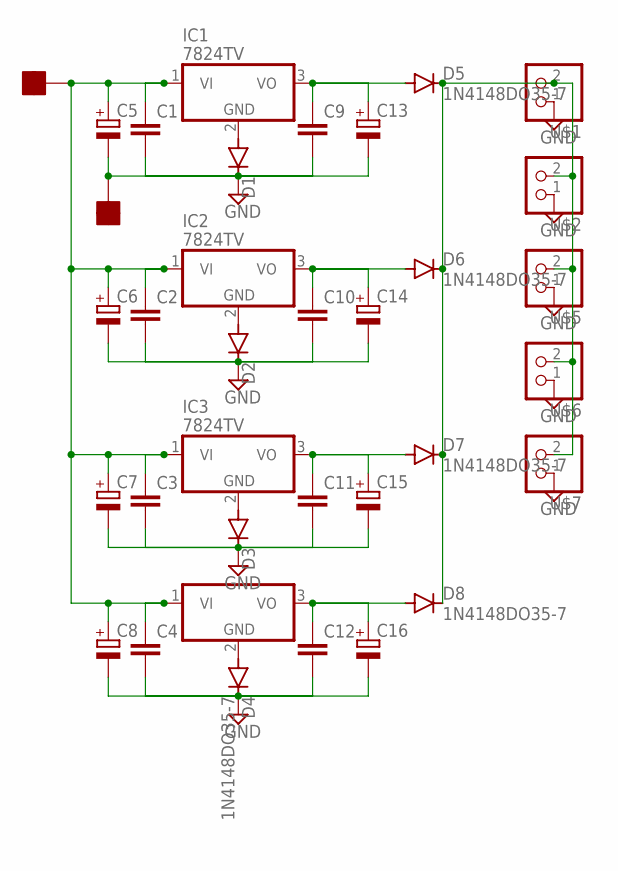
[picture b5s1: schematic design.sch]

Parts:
C1, C2, C3, C4, C9, C10, C11, C12: C-EU025-024X044; C025-024X044
C5, C6, C7, C8, C13, C14, C15, C16: CPOL-EUE2.5-7; E2,5-7
D1, D2, D3, D4, D5, D6, D7, D8: 1N4148DO35-7; DO35-7
IC1, IC2, IC3, IC4: 7824TV; TO220V
U$1, U$2, U$5, U$6, U$7: ABOUTERS_2PIN; 22-23-2021
U$3, U$4: PLAT10.0X10.0; PLAT

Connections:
GND: C1.2, C2.2, C3.2, C4.2, C5.-, C6.-, C7.-, C8.-, C9.2, C10.2, C11.2, C12.2, C13.-, C14.-, C15.-, C16.-, D1.C, D2.C, D3.C, D4.C, U$1.1, U$2.1, U$4.P$1, U$5.1, U$6.1, U$7.1
unnamed: D1.A, IC1.2 (GND)
unnamed: D2.A, IC2.2 (GND)
unnamed: D3.A, IC3.2 (GND)
unnamed: D4.A, IC4.2 (GND)
unnamed: C11.1, C15.+, D7.A, IC3.3 (VO)
unnamed: C1.1, C2.1, C3.1, C4.1, C5.+, C6.+, C7.+, C8.+, IC1.1 (VI), IC2.1 (VI), IC3.1 (VI), IC4.1 (VI), U$3.P$1
unnamed: C10.1, C14.+, D6.A, IC2.3 (VO)
unnamed: C9.1, C13.+, D5.A, IC1.3 (VO)
unnamed: C12.1, C16.+, D8.A, IC4.3 (VO)
unnamed: D5.C, D6.C, D7.C, D8.C, U$1.2, U$2.2, U$5.2, U$6.2, U$7.2

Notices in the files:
parts and their libraries:
diy-modules: Released under the Creative Commons Attribution 4.0 International License: http://creativecommons.org/licenses/by/4.0
